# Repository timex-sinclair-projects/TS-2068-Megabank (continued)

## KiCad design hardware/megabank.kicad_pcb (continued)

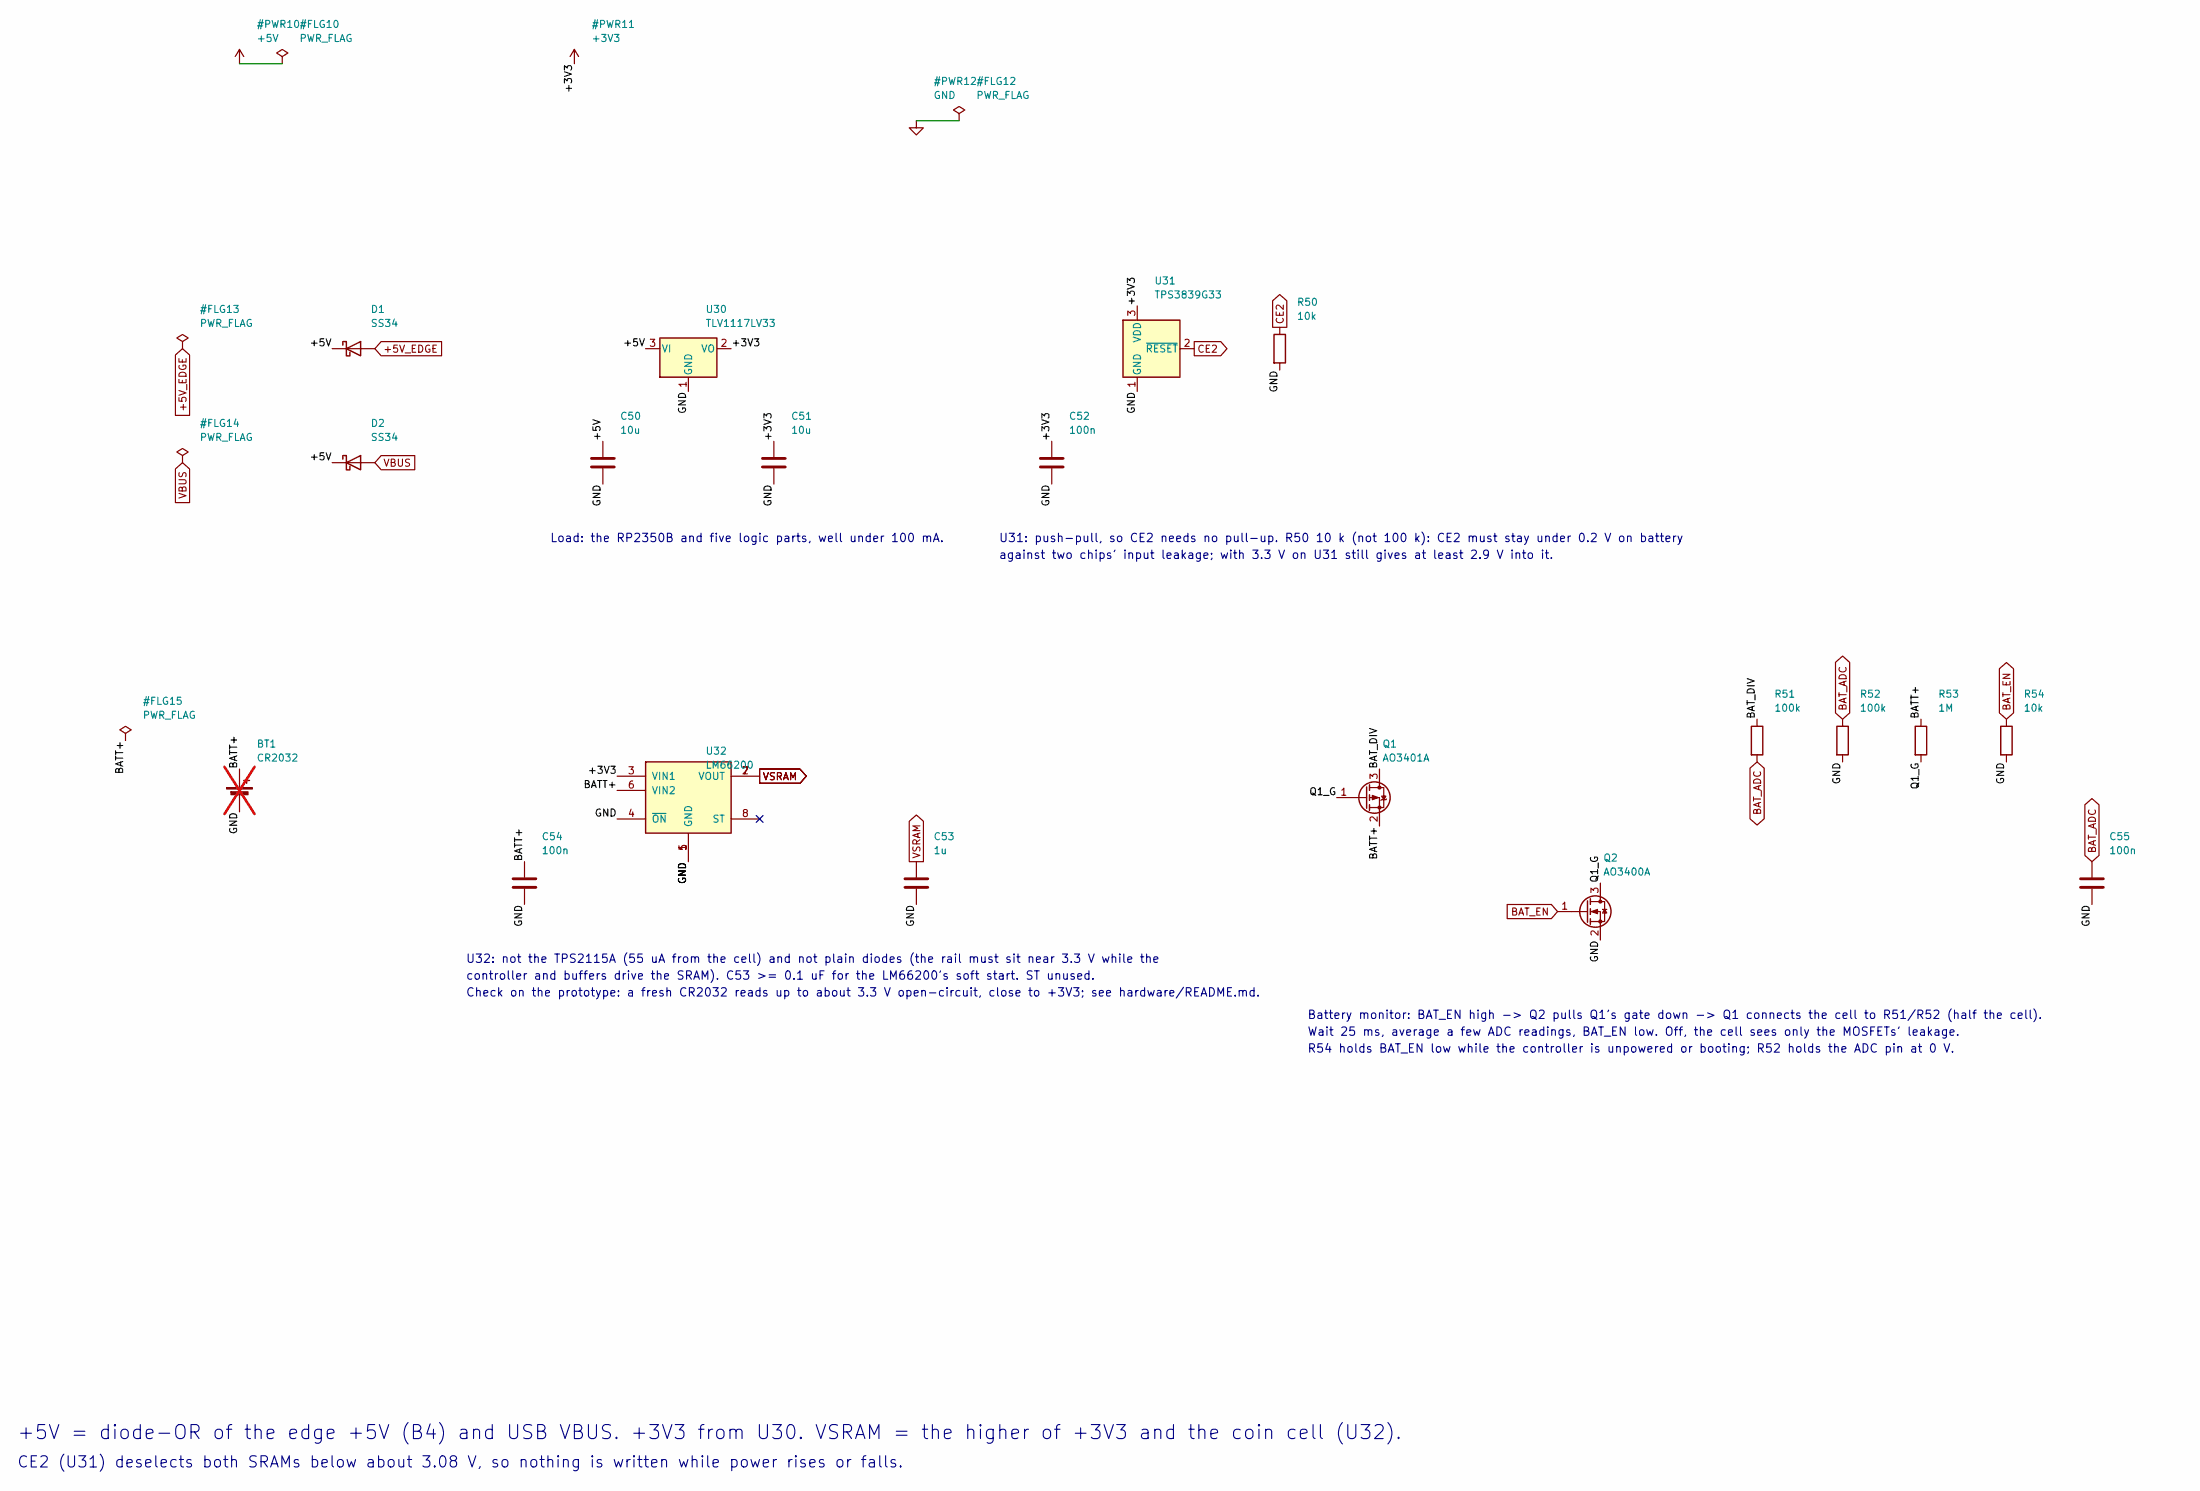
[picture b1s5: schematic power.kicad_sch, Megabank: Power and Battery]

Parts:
BT1: CR2032; BatteryHolder_Keystone_3034_1x20mm; MPN 3034; not fitted
C50, C51: 10u; C_0603_1608Metric; MPN CL10A106KP8NNNC; LCSC C19702
C52, C54, C55: 100n; C_0603_1608Metric; MPN CC0603KRX7R9BB104; LCSC C14663
C53: 1u; C_0603_1608Metric; MPN CL10A105KB8NNNC; LCSC C15849
D1, D2: SS34; D_SMA; MPN SS34; LCSC C8678
Q1: AO3401A; SOT-23; MPN AO3401A; LCSC C15127
Q2: AO3400A; SOT-23; MPN AO3400A; LCSC C20917
R50, R54: 10k; R_0603_1608Metric; MPN 0603WAF1002T5E; LCSC C25804
R51, R52: 100k; R_0603_1608Metric; MPN 0603WAF1003T5E; LCSC C25803
R53: 1M; R_0603_1608Metric; MPN 0603WAF1004T5E; LCSC C22935
U30: TLV1117LV33; SOT-223-3_TabPin2; MPN TLV1117LV33DCYR; LCSC C15578
U31: TPS3839G33; SOT-23; MPN TPS3839G33DBZR; LCSC C485802
U32: LM66200; SOT-583-8; MPN LM66200DRLR; LCSC C3235556

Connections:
+3V3: C51.1, C52.1, U30.2 (VO), U31.3 (VDD), U32.3 (VIN1); also elsewhere on the board
+5V: C50.1, D1.1 (K), D2.1 (K), U30.3 (VI)
+5V_EDGE: D1.2 (A); also elsewhere on the board
/Power and Battery/BATT+: BT1.1 (+), C54.1, Q1.2 (S), R53.1, U32.6 (VIN2)
/Power and Battery/BAT_DIV: Q1.3 (D), R51.1
/Power and Battery/Q1_G: Q1.1 (G), Q2.3 (D), R53.2
BAT_ADC: C55.1, R51.2, R52.1; also elsewhere on the board
BAT_EN: Q2.1 (G), R54.1; also elsewhere on the board
CE2: R50.1, U31.2 (~RESET); also elsewhere on the board
GND: BT1.2 (-), C50.2, C51.2, C52.2, C53.2, C54.2, C55.2, Q2.2 (S), R50.2, R52.2, R54.2, U30.1 (GND), U31.1 (GND), U32.1 (GND), U32.4 (~ON), U32.5 (GND); also elsewhere on the board
VBUS: D2.2 (A); also elsewhere on the board
VSRAM: C53.1, U32.2 (VOUT), U32.7 (VOUT); also elsewhere on the board

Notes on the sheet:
+5V = diode-OR of the edge +5V (B4) and USB VBUS. +3V3 from U30. VSRAM = the higher of +3V3 and the coin cell (U32).
CE2 (U31) deselects both SRAMs below about 3.08 V, so nothing is written while power rises or falls.
Load: the RP2350B and five logic parts, well under 100 mA.
U31: push-pull, so CE2 needs no pull-up. R50 10 k (not 100 k): CE2 must stay under 0.2 V on battery
against two chips' input leakage; with 3.3 V on U31 still gives at least 2.9 V into it.
U32: not the TPS2115A (55 uA from the cell) and not plain diodes (the rail must sit near 3.3 V while the
controller and buffers drive the SRAM). C53 >= 0.1 uF for the LM66200's soft start. ST unused.
Check on the prototype: a fresh CR2032 reads up to about 3.3 V open-circuit, close to +3V3; see hardware/README.md.
Battery monitor: BAT_EN high -> Q2 pulls Q1's gate down -> Q1 connects the cell to R51/R52 (half the cell).
Wait 25 ms, average a few ADC readings, BAT_EN low. Off, the cell sees only the MOSFETs' leakage.
R54 holds BAT_EN low while the controller is unpowered or booting; R52 holds the ADC pin at 0 V.

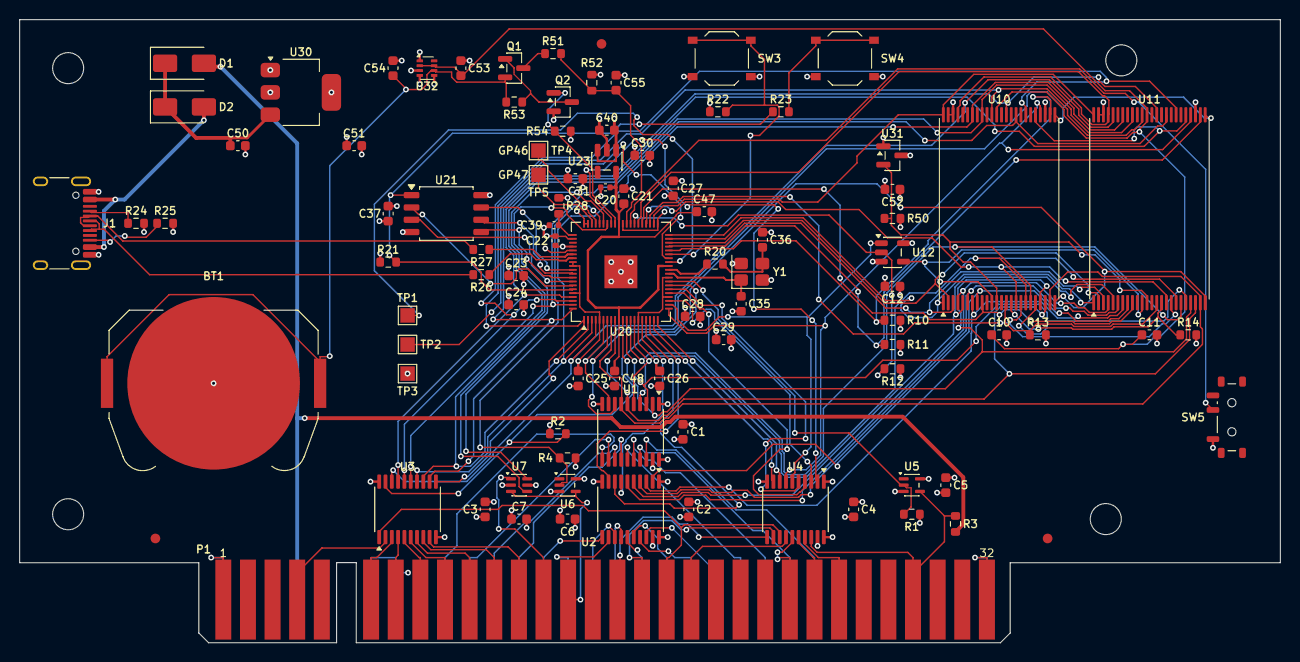
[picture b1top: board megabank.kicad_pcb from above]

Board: 4 copper layers, 130.0 x 64.2 mm, 97 parts (0 on the bottom side), 121 nets.

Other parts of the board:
FID1, FID2, FID3: Fiducial_1mm_Mask2mm
H1, H2, H3, H4: MountingHole_3.2mm_M3

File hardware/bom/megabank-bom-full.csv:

"Value","Reference","Footprint","MPN","LCSC","Qty"
"100n","C1-C7,C10-C12,C21,C23-C31,C37,C47,C48,C52,C54,C55","Capacitor_SMD:C_0603_1608Metric","CC0603KRX7R9BB104","C14663","26"
"4.7u","C20,C22,C39","Capacitor_SMD:C_0402_1005Metric","CL05A475MP5NRNC","C23733","3"
"15p","C35,C36","Capacitor_SMD:C_0603_1608Metric","CL10C150JB8NNNC","C1644","2"
"1u","C40,C53","Capacitor_SMD:C_0603_1608Metric","CL10A105KB8NNNC","C15849","2"
"10u","C50,C51","Capacitor_SMD:C_0603_1608Metric","CL10A106KP8NNNC","C19702","2"
"SS34","D1,D2","Diode_SMD:D_SMA","SS34","C8678","2"
"USB-C","J1","Connector_USB:USB_C_Receptacle_HRO_TYPE-C-31-M-12","TYPE-C-31-M-12","C165948","1"
"TS2068_Edge","P1","megabank:TS2068_EdgeConnector_2x32","","","1"
"AO3401A","Q1","Package_TO_SOT_SMD:SOT-23","AO3401A","C15127","1"
"AO3400A","Q2","Package_TO_SOT_SMD:SOT-23","AO3400A","C20917","1"
"10k","R1,R2,R4,R10-R12,R21,R22,R50,R54","Resistor_SMD:R_0603_1608Metric","0603WAF1002T5E","C25804","10"
"0","R13,R14","Resistor_SMD:R_0603_1608Metric","0603WAF0000T5E","C21189","2"
"1k","R20,R23","Resistor_SMD:R_0603_1608Metric","0603WAF1001T5E","C21190","2"
"5k1","R24,R25","Resistor_SMD:R_0603_1608Metric","0603WAF5101T5E","C23186","2"
"33","R26-R28","Resistor_SMD:R_0603_1608Metric","0603WAF330JT5E","C23140","3"
"100k","R51,R52","Resistor_SMD:R_0603_1608Metric","0603WAF1003T5E","C25803","2"
"1M","R53","Resistor_SMD:R_0603_1608Metric","0603WAF1004T5E","C22935","1"
"RUN","SW3","Button_Switch_SMD:SW_Push_1P1T_XKB_TS-1187A","TS-1187A-B-A-B","C318884","1"
"BOOTSEL","SW4","Button_Switch_SMD:SW_Push_1P1T_XKB_TS-1187A","TS-1187A-B-A-B","C318884","1"
"WP","SW5","Button_Switch_SMD:SW_SPDT_Shouhan_MSK12C02","MSK12C02","C431540","1"
"SWCLK","TP1","TestPoint:TestPoint_Pad_1.5x1.5mm","","","1"
"SWDIO","TP2","TestPoint:TestPoint_Pad_1.5x1.5mm","","","1"
"GND","TP3","TestPoint:TestPoint_Pad_1.5x1.5mm","","","1"
"GP46","TP4","TestPoint:TestPoint_Pad_1.5x1.5mm","","","1"
"GP47","TP5","TestPoint:TestPoint_Pad_1.5x1.5mm","","","1"
"74LVC245APW","U1-U4","Package_SO:TSSOP-20_4.4x6.5mm_P0.65mm","74LVC245APW,118","C6082","4"
"74LVC1G06","U5,U6","Package_TO_SOT_SMD:SOT-353_SC-70-5","SN74LVC1G06DCKR","C7828","2"
"74LVC2G34","U7","Package_TO_SOT_SMD:SOT-363_SC-70-6","SN74LVC2G34DCKR","C14461","1"
"CY62167EV30LL-45ZXIT","U10,U11","Package_SO:TSOP-I-48_18.4x12mm_P0.5mm","CY62167EV30LL-45ZXIT","C511152","2"
"SN74LVC1G32DBVR","U12","Package_TO_SOT_SMD:SOT-23-5","SN74LVC1G32DBVR","C10096","1"
"RP2350B","U20","Package_DFN_QFN:QFN-80-1EP_10x10mm_P0.4mm_EP3.4x3.4mm","RP2350B","C42415655","1"
"GD25Q128ESIGR","U21","Package_SO:SOIC-8_5.3x5.3mm_P1.27mm","GD25Q128ESIGR","C2928891","1"
"ME6211C12M5G-N","U23","Package_TO_SOT_SMD:SOT-23-5","ME6211C12M5G-N","C236672","1"
"TLV1117LV33","U30","Package_TO_SOT_SMD:SOT-223-3_TabPin2","TLV1117LV33DCYR","C15578","1"
"TPS3839G33","U31","Package_TO_SOT_SMD:SOT-23","TPS3839G33DBZR","C485802","1"
"LM66200","U32","Package_TO_SOT_SMD:SOT-583-8","LM66200DRLR","C3235556","1"
"12MHz","Y1","Crystal:Crystal_SMD_3225-4Pin_3.2x2.5mm","ABM8-272-T3","C20625731","1"

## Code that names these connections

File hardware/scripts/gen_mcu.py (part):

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Dropped from v3: the PSRAM (U22, C38) and the core regulator's inductor L1. Added: SW5,
the write-protect switch; U23, an ME6211C12 LDO that supplies DVDD at 1.2 V in place of
the on-chip switcher (RP2350 datasheet 6.3.7; as on the OpenSpand card), with C40 at its
input and C20 at its output; TP4/TP5 on the spare GPIO46/47, for bench experiments.

GPIO map (docs/spec.md "Pins"). PIO windows: a state machine sees 32 pins, from GPIO0
or GPIO16, so everything both programs need sits in GPIO16-31:
  GPIO0-7    SD0-SD7       SRAM-side data (port reads and writes)        window 0
  GPIO8-15   BA0-BA7       port decode                                     window 0
  GPIO16-18  BA13-BA15     chunk number (out pc, 3)                        both
  GPIO19-25  nMREQ_L nIORQ_L nRD_L nWR_L nRFSH_L nM1_L nRESET_L            both
  GPIO26     nDOE          data buffer enable (R2 pull-up)                 both
  GPIO27     BE_REQ        to U5 -> /BE (R1 pull-down)                     both
  GPIO28-29  nCE1_0/1      SRAM chip enables (R10/R11 pull-downs)          window 16
  GPIO30-37  PA13-PA20     page bits, contiguous after the ~CE1s           window 16
  GPIO38     WINH          write inhibit (R12 pull-up)                     window 16
  GPIO39     nWP           write-protect switch, low = protected (internal pull-up)
  GPIO40     BAT_ADC       ADC0
  GPIO41     BAT_EN
  GPIO42     nBE_L         /BE read back
  GPIO43     nINT_L        /INT, through U7                                window 16
  GPIO44     nNMI_L        /NMI, through U7                                window 16
  GPIO45     NMI_REQ       to U6 -> /NMI (R4 pull-down)                    window 16
  GPIO46-47  GP46, GP47    spare, to test pads TP4/TP5 (bench experiments)
"""
import os
import sys
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        if nm in ("IOVDD", "QSPI_IOVDD", "USB_OTP_VDD", "ADC_AVDD", "VREG_VIN"):
            s.label("+3V3", U.pin(num))
        elif nm == "VREG_AVDD":
            s.label("VREG_AVDD", U.pin(num))
        elif nm in ("GND", "VREG_PGND"):
            s.label("GND", U.pin(num))
        elif nm == "DVDD":
            s.label("DVDD", U.pin(num))
    s.nc(U.pin(by_name["VREG_LX"]))                 # on-chip switcher unused: no inductor
    s.label("GND", U.pin(by_name["VREG_FB"]))       # datasheet 6.3.7: FB to ground when DVDD comes from outside
    s.label("XIN", U.pin(by_name["XIN"])); s.label("XOUT", U.pin(by_name["XOUT"]))
    s.label("SWCLK", U.pin(by_name["SWCLK"])); s.label("SWDIO", U.pin(by_name["SWDIO"]))
    s.label("RUN", U.pin(by_name["RUN"]))
    s.label("USB_DM", U.pin(by_name["USB_DM"])); s.label("USB_DP", U.pin(by_name["USB_DP"]))
    for nm in ("QSPI_SD0", "QSPI_SD1", "QSPI_SD2", "QSPI_SD3", "QSPI_SCLK"):
        s.label(nm, U.pin(by_name[nm]))
    s.label("nQSPI_SS", U.pin(by_name["~{QSPI_SS}"]))

    # ---- core supply: ME6211C12 LDO (U23) -> DVDD 1.2 V, in place of the on-chip switcher ----------
    # The switcher's inductor (Abracon AOTA-B201610, L1 on v3) is the scarcest part on the board, so
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    # stay powered: the chip's power-on reset runs from them. Firmware may put the regulator in HIZ.
    LDO = s.place("Regulator_Linear:ME6211C12M5", "U23", "ME6211C12M5G-N", SOT23_5, 250, 60)
    s.label("+3V3", LDO.pin("1")); s.label("GND", LDO.pin("2")); s.label("+3V3", LDO.pin("3"))
    s.nc(LDO.pin("4")); s.label("DVDD", LDO.pin("5"))
    for k, (ref, net, val, fp) in enumerate([("C40", "+3V3", "1u", C0603), ("C20", "DVDD", "4.7u", C0402), ("C22", "+3V3", "4.7u", C0402), ("C21", "DVDD", "100n", C0603), ("C47", "DVDD", "100n", C0603), ("C48", "DVDD", "100n", C0603)]):
        C = s.place("Device:C", ref, val, fp, 265 + 10 * k, 60)
        s.label(net, C.pin("1")); s.label("GND", C.pin("2"))
    s.text("U23 ME6211C12M5G-N: DVDD 1.2 V (v3 runs the core at 1.2 V for 250 MHz). C40 1 uF in, C20 4.7 uF out. VREG_LX open, VREG_FB to GND.", 245, 75, 1.5)
    s.text("C22 at VREG_VIN (0402 as in the design guide). C21/C47/C48: 100 nF at DVDD pins 51, 32, 10.", 245, 78, 1.5)
    R28 = s.place("Device:R", "R28", "33", R0603, 300, 85)
    s.label("+3V3", R28.pin("1")); s.label("VREG_AVDD", R28.pin("2"))
    C39 = s.place("Device:C", "C39", "4.7u", C0402, 315, 85)
    s.label("VREG_AVDD", C39.pin("1")); s.label("GND", C39.pin("2"))
    s.text("R28/C39: 33 R + 4.7 uF filter on VREG_AVDD (design guide R3/C9).", 245, 95, 1.5)
    FL2 = s.place("power:PWR_FLAG", "#FLG08", "PWR_FLAG", "", 330, 85)
    s.label("VREG_AVDD", FL2.pin("1"))

    # ---- IOVDD and analog decoupling: 12 x 100 nF ----------------------------------
    for k in range(9):
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
    # ---- crystal ---------------------------------------------------------------------
    Y1 = s.place("Device:Crystal_GND24", "Y1", "12MHz", "Crystal:Crystal_SMD_3225-4Pin_3.2x2.5mm", 270, 150)
    s.label("XIN", Y1.pin("1")); s.label("XOUT_R", Y1.pin("3")); s.label("GND", Y1.pin("2")); s.label("GND", Y1.pin("4"))
    R20 = s.place("Device:R", "R20", "1k", R0603, 295, 150)
    s.label("XOUT", R20.pin("1")); s.label("XOUT_R", R20.pin("2"))
    C35 = s.place("Device:C", "C35", "15p", C0603, 255, 165)
    s.label("XIN", C35.pin("1")); s.label("GND", C35.pin("2"))
    C36 = s.place("Device:C", "C36", "15p", C0603, 285, 165)
    s.label("XOUT_R", C36.pin("1")); s.label("GND", C36.pin("2"))
    s.text("Y1: 12 MHz, e.g. ABM8-272-T3 (CL 10 pF). C35/C36 15 pF, R20 1 k in series with XOUT.", 245, 180, 1.5)

    # ---- QSPI flash and PSRAM ---------------------------------------------------------
    F = s.place("Memory_Flash:W25Q128JVS", "U21", "GD25Q128ESIGR", "Package_SO:SOIC-8_5.3x5.3mm_P1.27mm", 340, 150)
    s.label("nQSPI_SS", F.pin("1")); s.label("QSPI_SD1", F.pin("2")); s.label("QSPI_SD2", F.pin("3")); s.label("GND", F.pin("4"))
    s.label("QSPI_SD0", F.pin("5")); s.label("QSPI_SCLK", F.pin("6")); s.label("QSPI_SD3", F.pin("7")); s.label("+3V3", F.pin("8"))
    C = s.place("Device:C", "C37", "100n", C0603, 375, 175)
    s.label("+3V3", C.pin("1")); s.label("GND", C.pin("2"))
    R21 = s.place("Device:R", "R21", "10k", R0603, 395, 150)
    s.label("+3V3", R21.pin("1")); s.label("nQSPI_SS", R21.pin("2"))
    s.text("U21 boot flash (XIP CS0), C37 at U21. Holds the firmware and the settings (BASE, SIZE).", 320, 225, 1.5)

    # ---- RUN and BOOTSEL -------------------------------------------------------------
    R22 = s.place("Device:R", "R22", "10k", R0603, 250, 210)
    s.label("+3V3", R22.pin("1")); s.label("RUN", R22.pin("2"))
    SW3 = s.place("Switch:SW_Push", "SW3", "RUN", SW_FP, 270, 225)
    s.label("RUN", SW3.pin("1")); s.label("GND", SW3.pin("2"))
    R23 = s.place("Device:R", "R23", "1k", R0603, 250, 245)
    s.label("nQSPI_SS", R23.pin("1")); s.label("BOOTSEL_SW", R23.pin("2"))
    SW4 = s.place("Switch:SW_Push", "SW4", "BOOTSEL", SW_FP, 270, 260)
    s.label("BOOTSEL_SW", SW4.pin("1")); s.label("GND", SW4.pin("2"))

    # ---- USB-C, data only -----------------------------------------------------------
    J1 = s.place("Connector:USB_C_Receptacle_USB2.0_16P", "J1", "USB-C", "Connector_USB:USB_C_Receptacle_HRO_TYPE-C-31-M-12", 40, 60)
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        s.nc(J1.pin(pin))
    for pin in ("A1", "A12", "B1", "B12", "SH"):
        s.label("GND", J1.pin(pin))
    s.label("USB_DP_C", J1.pin("A6")); s.label("USB_DP_C", J1.pin("B6"))
    s.label("USB_DM_C", J1.pin("A7")); s.label("USB_DM_C", J1.pin("B7"))
    s.label("CC1", J1.pin("A5")); s.label("CC2", J1.pin("B5"))
    R24 = s.place("Device:R", "R24", "5k1", R0603, 80, 40)
    s.label("CC1", R24.pin("1")); s.label("GND", R24.pin("2"))
    R25 = s.place("Device:R", "R25", "5k1", R0603, 95, 40)
    s.label("CC2", R25.pin("1")); s.label("GND", R25.pin("2"))
    R26 = s.place("Device:R", "R26", "33", R0603, 80, 85)
    s.label("USB_DP_C", R26.pin("1")); s.label("USB_DP", R26.pin("2"))
    R27 = s.place("Device:R", "R27", "33", R0603, 95, 85)
    s.label("USB_DM_C", R27.pin("1")); s.label("USB_DM", R27.pin("2"))
    s.text("J1: USB 2.0. VBUS -> power sheet. SBU unconnected.", 20, 100, 1.5)
    s.text("R24/R25 5.1 k Rd. R26/R27 33 R series (JLC basic; 27 R is not).", 20, 103, 1.5)

    # ---- write-protect switch -------------------------------------------------------
    SW5 = s.place("Switch:SW_SPDT", "SW5", "WP", SLIDE_FP, 270, 280)
    s.glabel("nWP", SW5.pin("B"), IN); s.label("GND", SW5.pin("A")); s.nc(SW5.pin("C"))
    s.text("SW5: write protect. Common to GPIO39 (internal pull-up); one throw to ground = protected, the other open.", 245, 292, 1.5)

    # ---- SWD pads ---------------------------------------------------------------------
    for k, (ref, net) in enumerate([("TP1", "SWCLK"), ("TP2", "SWDIO"), ("TP3", "GND")]):
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    for k, (ref, net) in enumerate([("TP4", "GP46"), ("TP5", "GP47")]):
        T = s.place("Connector:TestPoint", ref, net, TP_FP, 100 + 15 * k, 250)
        s.label(net, T.pin("1"))
    s.text("TP4/TP5: spare GPIO46/47, for bench experiments (a second controller's handshake).", 90, 262, 1.5)

    s.write()
    print("wrote mcu.kicad_sch")
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
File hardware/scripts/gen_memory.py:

#!/usr/bin/env python3
"""Generate memory.kicad_sch: the 4 MB of SRAM.

  U10, U11  CY62167EV30LL-45ZXIT (16 Mbit, TSOP I 48), each used as 2M x 8: BYTE to
            ground, pin 45 (I/O15/A20) is A20, I/O8-I/O14 unused. 4 MB in two chips.
            A0-A12   <- BA0-BA12, the buffered Z80 address
            A13-A20  <- PA13-PA20, the page bits from the controller
            I/O0-7  <-> SD0-SD7, the data buffer's SRAM side (and the controller's GPIO0-7)
            ~CE1     <- nCE1_0 / nCE1_1 from the controller: the 9th page bit picks the chip
            CE2      <- CE2 from the supervisor (power sheet): low deselects whatever ~CE1 does
            ~OE      <- nRD_L;  ~WE <- nSWE from U12
            VCC      <- VSRAM, the battery-backed rail
  U12       SN74LVC1G32: nSWE = nWR_L OR WINH (the controller's per-chunk write inhibit)
  R10, R11  ~CE1 pull-downs: at a logic level on battery (a pull-up to VSRAM would feed the
            unpowered RP2350B); CE2 low keeps the chips deselected
  R12       WINH pull-up: Z80 writes cannot reach the SRAM until the firmware runs
  R13, R14  0 R, BHE and BLE to ground: fitted for the EV30 (needs them at a logic level
            for its standby figures), do not place for a DV30 (marks them "leave floating")
SRAM address and data lines may be permuted freely at layout (both chips see the same
permutation through the same Z80 and page bits), except that SDn must stay the
controller's GPIOn: the controller answers IN FCh/FDh on the same bus.
"""
import os
import sys

sys.path.insert(0, os.path.dirname(os.path.abspath(__file__)))
from schlib import Sheet  # noqa: E402

TSOP48 = "Package_SO:TSOP-I-48_18.4x12mm_P0.5mm"
SOT23_5 = "Package_TO_SOT_SMD:SOT-23-5"
R0603 = "Resistor_SMD:R_0603_1608Metric"
C0603 = "Capacitor_SMD:C_0603_1608Metric"

OUT, IN, BI = "output", "input", "bidirectional"


def main():
    s = Sheet("megabank.kicad_sch", "memory.kicad_sch", "Megabank: SRAM")
    s.text("4 MB: two CY62167EV30 as 2M x 8. SRAM address = page x 8K + A12..A0; the page's 9th bit picks the chip through the ~CE1s.", 20, 285, 2.5)
    s.text("Alternate fit: CY62167DV30LL-55ZXIT, same footprint and pinout; leave R13 and R14 off for it.", 20, 290, 2.0)

    s.power("+3V3", 330, 30, "#PWR03", flag=False)
    s.power("GND", 360, 40, "#PWR04", flag=False)

    for k, (ref, ce1) in enumerate((("U10", "nCE1_0"), ("U11", "nCE1_1"))):
        U = s.place("megabank:CY62167EV30xx-ZXI", ref, "CY62167EV30LL-45ZXIT", TSOP48, 80 + 120 * k, 130)
        for i in range(13):
            s.glabel(f"BA{i}", U.pin(f"A{i}"), IN)
        for i in range(13, 20):
            s.glabel(f"PA{i}", U.pin(f"A{i}"), IN)
        s.glabel("PA20", U.pin("I/O15/A20"), IN)
        for i in range(8):
            s.glabel(f"SD{i}", U.pin(f"I/O{i}"), BI)
        for i in range(8, 15):
            s.nc(U.pin(f"I/O{i}"))
        s.glabel(ce1, U.pin("~{CE1}"), IN)
        s.glabel("CE2", U.pin("CE2"), IN)
        s.glabel("nRD_L", U.pin("~{OE}"), IN)
        s.label("nSWE", U.pin("~{WE}"))
        s.label("BHE", U.pin("~{BHE}")); s.label("BLE", U.pin("~{BLE}"))
        s.label("GND", U.pin("BYTE"))
        s.glabel("VSRAM", U.pin("37"), IN)
        s.label("GND", U.pin("27")); s.label("GND", U.pin("46"))

    # ---- /WE gate ---------------------------------------------------------------
    U12 = s.place("74xGxx:74LVC1G32", "U12", "SN74LVC1G32DBVR", SOT23_5, 320, 120)
    s.glabel("nWR_L", U12.pin("1"), IN); s.glabel("WINH", U12.pin("2"), IN); s.label("nSWE", U12.pin("4"))
    s.label("+3V3", U12.pin("5")); s.label("GND", U12.pin("3"))
    s.text("U12: ~WE = nWR_L OR WINH. WINH is set per chunk from WPROT and the switch, and pulled up (R12).", 290, 135, 1.5)

    # ---- pulls and the BHE/BLE links ------------------------------------------------
    pulls = [("R10", "nCE1_0", "GND", "10k"), ("R11", "nCE1_1", "GND", "10k"), ("R12", "WINH", "+3V3", "10k"),
             ("R13", "BHE", "GND", "0"), ("R14", "BLE", "GND", "0")]
    for k, (ref, net, rail, val) in enumerate(pulls):
        R = s.place("Device:R", ref, val, R0603, 300 + 15 * k, 170)
        if net in ("BHE", "BLE"):
            s.label(net, R.pin("1"))
        else:
            s.glabel(net, R.pin("1"), IN)
        s.label(rail, R.pin("2"))
    s.text("R10/R11: ~CE1 pull-downs (to ground, not VSRAM). R13/R14: fit for the EV30, DNP for a DV30 build.", 290, 185, 1.5)

    # ---- decoupling: 100 nF at each SRAM (VSRAM), 100 nF at U12 ----------------------
    for k, (ref, net) in enumerate((("C10", "VSRAM"), ("C11", "VSRAM"), ("C12", "+3V3"))):
        C = s.place("Device:C", ref, "100n", C0603, 40 + 9 * k, 255)
        if net == "VSRAM":
            s.glabel(net, C.pin("1"), IN)
        else:
            s.label(net, C.pin("1"))
        s.label("GND", C.pin("2"))

    s.write()
    print("wrote memory.kicad_sch")


if __name__ == "__main__":
    main()

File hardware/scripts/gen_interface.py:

#!/usr/bin/env python3
"""Generate interface.kicad_sch: the 2068 side of the Megabank.

Contents (docs/spec.md, "Hardware"):
  P1   TS2068 edge connector (v3's gold fingers)
  U1   74LVC245  Z80 A0-A7  -> BA0-BA7     always on (fixed B->A): port decode, SRAM A0-A7
  U2   74LVC245  Z80 A8-A15 -> BA8-BA15    always on: SRAM A8-A12, chunk A13-A15
  U3   74LVC245  Z80 D0-D7 <-> SD0-SD7     DIR = /RD, /OE = nDOE from the controller
  U4   74LVC245  Z80 control -> 3.3 V copies for the controller (fixed B->A)
  U5   74LVC1G06 open-drain inverter: BE_REQ -> /BE (wire-ORs with v3's 74LVC06)
  R1   BE_REQ pull-down (boot does not rely on the RP2350's internal pull-down, erratum E9)
  R2   nDOE pull-up: the data buffer stays off the bus until the firmware runs
  R3   /BE pull-up to the 2068's +5V, DNP: the bus already has v3's 2k2 (R14 on v3);
       fit it only if open question 13 says the board needs its own
  U6   74LVC1G06 open-drain inverter: NMI_REQ -> /NMI (wire-ORs with v3's NMI driver and button)
  R4   NMI_REQ pull-down, as R1
  U7   74LVC2G34 /INT and /NMI -> 3.3 V copies (nINT_L, nNMI_L) for the controller
       (spec, open question 16). /NMI's pull-up is the 2068's own, as for v3.
Unlike v3 the address buffers are not a byte mux: the SRAM needs A0-A12 on
every memory cycle, so every address bit has its own 3.3 V net (BAn).
Net naming: n<NAME> = active low; _L = 3.3 V copy of a bus signal.
"""
import os
import sys

sys.path.insert(0, os.path.dirname(os.path.abspath(__file__)))
from schlib import Sheet  # noqa: E402

TSSOP20 = "Package_SO:TSSOP-20_4.4x6.5mm_P0.65mm"
SC70_5 = "Package_TO_SOT_SMD:SOT-353_SC-70-5"
SC70_6 = "Package_TO_SOT_SMD:SOT-363_SC-70-6"
R0603 = "Resistor_SMD:R_0603_1608Metric"
C0603 = "Capacitor_SMD:C_0603_1608Metric"

OUT, IN, BI = "output", "input", "bidirectional"


def main():
    s = Sheet("megabank.kicad_sch", "interface.kicad_sch", "Megabank: 2068 Interface")
    s.text("2068 bus interface. Nets: n = active low, _L = 3.3 V copy of a bus signal, BAn = buffered address, SDn = SRAM-side data.", 20, 285, 2.5)
    s.text("Power: edge +5V (B4) goes to the power sheet as +5V_EDGE. +15V (B3) unused. LVC inputs take the 2068's 5 V; a 3.3 V high is a TTL high.", 20, 290, 2.0)

    # ---- P1 edge connector -------------------------------------------------
    P1 = s.place("megabank:TS2068_Edge", "P1", "TS2068_Edge", "megabank:TS2068_EdgeConnector_2x32", 60, 120)
    used = {
        "A1": "GND", "B1": "GND", "A32": "GND", "B32": "GND", "B7": "GND", "B8": "GND",
        "A4": "D7", "A7": "D0", "A8": "D1", "A9": "D2", "A10": "D6", "A11": "D5", "A12": "D3", "A13": "D4",
        "A17": "nMREQ", "A18": "nIORQ", "A19": "nRD", "A20": "nWR", "A24": "nRESET",
        "A25": "nM1", "A26": "nRFSH", "A29": "nBE", "A14": "nINT", "A15": "nNMI",
        "B10": "A0", "B11": "A1", "B12": "A2", "B13": "A3",
        "B14": "A15", "B15": "A14", "B16": "A13", "B17": "A12", "B18": "A11", "B19": "A10", "B20": "A9", "B21": "A8",
        "B22": "A7", "B23": "A6", "B24": "A5", "B25": "A4",
    }
    for pin, net in used.items():
        s.label(net, P1.pin(pin))
    s.glabel("+5V_EDGE", P1.pin("B4"), OUT)
    for side in "AB":
        for pos in range(1, 33):
            pin = f"{side}{pos}"
            if pos != 6 and pin not in used and pin != "B4":
                s.nc(P1.pin(pin))

    s.power("+3V3", 330, 30, "#PWR01", flag=False)
    s.power("GND", 360, 40, "#PWR02", flag=False)

    def transceiver(ref, x, y):
        return s.place("74xx:74LS245", ref, "74LVC245APW", TSSOP20, x, y)

    # ---- U1/U2 address buffers, B (Z80) -> A (3.3 V), always enabled ----------------
    # Finger order (left to right): A0 A1 A2 A3 | A15 ... A8 | A7 A6 A5 A4. As on v3, U2 sits
    # over the middle eight fingers and U1 in the row above, its B pins in finger order
    # (A0-A3 from the left, A7-A4 from the right); at rot 270 B7 is the leftmost pin.
    U1 = transceiver("U1", 150, 50)
    for b_, idx in zip(range(7, -1, -1), [0, 1, 2, 3, 7, 6, 5, 4]):
        s.label(f"A{idx}", U1.pin(f"B{b_}"))
        s.glabel(f"BA{idx}", U1.pin(f"A{b_}"), OUT)
    U2 = transceiver("U2", 150, 110)
    for b_, idx in zip(range(7, -1, -1), [15, 14, 13, 12, 11, 10, 9, 8]):
        s.label(f"A{idx}", U2.pin(f"B{b_}"))
        s.glabel(f"BA{idx}", U2.pin(f"A{b_}"), OUT)
    for U in (U1, U2):
        s.label("GND", U.pin("1"))       # DIR low: B -> A
        s.label("GND", U.pin("19"))      # always enabled
        s.label("+3V3", U.pin("20")); s.label("GND", U.pin("10"))

    # ---- U3 data transceiver: A = Z80 (faces the fingers), B = SD bus ---------------
    # DIR = /RD straight from the bus: low on a read = B -> A (board -> Z80). The SRAM's
    # data bits may be permuted freely at layout; the controller's GPIO0-7 may not.
    U3 = transceiver("U3", 150, 170)
    for b_, idx in zip(range(8), [7, 0, 1, 2, 6, 5, 3, 4]):
        s.label(f"D{idx}", U3.pin(f"A{b_}"))
        s.glabel(f"SD{idx}", U3.pin(f"B{b_}"), BI)
    s.label("nRD", U3.pin("1"))
    s.glabel("nDOE", U3.pin("19"), IN)
    s.label("+3V3", U3.pin("20")); s.label("GND", U3.pin("10"))

    # ---- U4 control inputs, B (Z80) -> A (3.3 V), in finger order ----------------------
    U4 = transceiver("U4", 150, 230)
    ctl = ["nMREQ", "nIORQ", "nRD", "nWR", "nRESET", "nM1", "nRFSH", "nBE"]
    for b_, src in zip(range(7, -1, -1), ctl):
        s.label(src, U4.pin(f"B{b_}"))
        s.glabel(src + "_L", U4.pin(f"A{b_}"), OUT)
    s.label("GND", U4.pin("1")); s.label("GND", U4.pin("19"))
    s.label("+3V3", U4.pin("20")); s.label("GND", U4.pin("10"))
    s.text("U4's eighth channel reads /BE back (nBE_L), for bench timing and to see v3 serving a chunk.", 120, 265, 1.5)

    # ---- U5 /BE driver ------------------------------------------------------------------
    U5 = s.place("74xGxx:74LVC1G06", "U5", "74LVC1G06", SC70_5, 260, 60)
    s.glabel("BE_REQ", U5.pin("2"), IN); s.label("nBE", U5.pin("4"))
    s.label("+3V3", U5.pin("5")); s.label("GND", U5.pin("3"))
    R1 = s.place("Device:R", "R1", "10k", R0603, 290, 60)
    s.glabel("BE_REQ", R1.pin("1"), IN); s.label("GND", R1.pin("2"))
    R2 = s.place("Device:R", "R2", "10k", R0603, 305, 60)
    s.label("+3V3", R2.pin("1")); s.glabel("nDOE", R2.pin("2"), IN)
    R3 = s.place("Device:R", "R3", "2k2", R0603, 320, 60, dnp=True)
    s.glabel("+5V_EDGE", R3.pin("1"), IN); s.label("nBE", R3.pin("2"))
    s.text("U5: open drain, so it wire-ORs with v3's 74LVC06 on /BE. R1: BE_REQ held low (released) until the firmware runs.", 245, 80, 1.5)
    s.text("R2: data buffer held off. R3 (DNP): /BE pull-up to the 2068's +5V, only if the bus's own (v3's 2k2) proves weak.", 245, 83, 1.5)

    # ---- /INT and /NMI: U6 /NMI driver, U7 input buffers ---------------------------------
    U6 = s.place("74xGxx:74LVC1G06", "U6", "74LVC1G06", SC70_5, 260, 120)
    s.glabel("NMI_REQ", U6.pin("2"), IN); s.label("nNMI", U6.pin("4"))
    s.label("+3V3", U6.pin("5")); s.label("GND", U6.pin("3"))
    R4 = s.place("Device:R", "R4", "10k", R0603, 290, 120)
    s.glabel("NMI_REQ", R4.pin("1"), IN); s.label("GND", R4.pin("2"))
    U7a = s.place("74xGxx:74LVC2G34", "U7", "74LVC2G34", SC70_6, 260, 150, unit=1)
    s.label("nINT", U7a.pin("1")); s.glabel("nINT_L", U7a.pin("6"), OUT)
    U7b = s.place("74xGxx:74LVC2G34", "U7", "74LVC2G34", SC70_6, 260, 165, unit=2)
    s.label("nNMI", U7b.pin("3")); s.glabel("nNMI_L", U7b.pin("4"), OUT)
    U7c = s.place("74xGxx:74LVC2G34", "U7", "74LVC2G34", SC70_6, 285, 157, unit=3)
    s.label("+3V3", U7c.pin("5")); s.label("GND", U7c.pin("2"))
    s.text("U6: open drain, like U5; R4 holds NMI_REQ low (released) until the firmware runs.", 245, 135, 1.5)
    s.text("U7: /INT and /NMI in, for the controller (spec, open question 16). /NMI's pull-up is the 2068's.", 245, 180, 1.5)

    # ---- decoupling ------------------------------------------------------------
    for k in range(7):          # C1-C4: U1-U4, C5-C7: U5-U7
        C = s.place("Device:C", f"C{k + 1}", "100n", C0603, 40 + 9 * k, 255)
        s.label("+3V3", C.pin("1")); s.label("GND", C.pin("2"))

    s.write()
    print("wrote interface.kicad_sch")


if __name__ == "__main__":
    main()

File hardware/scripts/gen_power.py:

#!/usr/bin/env python3
"""Generate power.kicad_sch: supplies, battery backup and the battery monitor.

  D1, D2   SS34: +5V_EDGE (edge pin B4) and USB VBUS diode-ORed into +5V, as on v3, so
           the board can be flashed and set up from USB alone on the bench
  U30      TLV1117LV33: +3V3 for the controller, buffers and gates
  U31      TPS3839G33 supervisor on +3V3 (about 3.08 V, 200 ms): drives both SRAMs' CE2
           high only while 3.3 V is good; R50 holds CE2 low with 3.3 V gone
  U32      LM66200 ideal-diode OR: VSRAM from +3V3 (VIN1) or the battery (VIN2), 1.32 uA
  BT1      CR2032 coin cell
  Q1, Q2   battery monitor switch (docs/spec.md "Battery monitor"): the cell is read
           straight off its terminal through R51/R52 only while BAT_EN is high
Spec refs in "Battery monitor" map to: Q1 -> Q1, Q2 -> Q2, R1/R2 -> R51/R52,
R3 -> R53, R4 -> R54, C1 -> C55.
"""
import os
import sys

sys.path.insert(0, os.path.dirname(os.path.abspath(__file__)))
from schlib import Sheet  # noqa: E402

C0603 = "Capacitor_SMD:C_0603_1608Metric"
R0603 = "Resistor_SMD:R_0603_1608Metric"
D_SMA = "Diode_SMD:D_SMA"
SOT223 = "Package_TO_SOT_SMD:SOT-223-3_TabPin2"
SOT23 = "Package_TO_SOT_SMD:SOT-23"
SOT583 = "Package_TO_SOT_SMD:SOT-583-8"
BAT_FP = "Battery:BatteryHolder_Keystone_3034_1x20mm"

OUT, IN, BI = "output", "input", "bidirectional"


def main():
    s = Sheet("megabank.kicad_sch", "power.kicad_sch", "Megabank: Power and Battery")
    s.text("+5V = diode-OR of the edge +5V (B4) and USB VBUS. +3V3 from U30. VSRAM = the higher of +3V3 and the coin cell (U32).", 20, 285, 2.5)
    s.text("CE2 (U31) deselects both SRAMs below about 3.08 V, so nothing is written while power rises or falls.", 20, 290, 2.0)

    s.power("+5V", 60, 40, "#PWR10")
    s.power("+3V3", 120, 40, "#PWR11", flag=False)   # driven by U30
    s.power("GND", 180, 50, "#PWR12")

    # ---- inputs -----------------------------------------------------------------
    D1 = s.place("Device:D_Schottky", "D1", "SS34", D_SMA, 80, 90)
    s.glabel("+5V_EDGE", D1.pin("A"), IN); s.label("+5V", D1.pin("K"))
    D2 = s.place("Device:D_Schottky", "D2", "SS34", D_SMA, 80, 110)
    s.glabel("VBUS", D2.pin("A"), IN); s.label("+5V", D2.pin("K"))
    F1 = s.place("power:PWR_FLAG", "#FLG13", "PWR_FLAG", "", 50, 90)
    s.glabel("+5V_EDGE", F1.pin("1"), IN)
    F2 = s.place("power:PWR_FLAG", "#FLG14", "PWR_FLAG", "", 50, 110)
    s.glabel("VBUS", F2.pin("1"), IN)

    # ---- U30 3.3 V LDO --------------------------------------------------------------
    U30 = s.place("Regulator_Linear:TLV1117-33", "U30", "TLV1117LV33", SOT223, 140, 90)
    s.label("+5V", U30.pin("VI")); s.label("+3V3", U30.pin("VO")); s.label("GND", U30.pin("GND"))
    for k, (ref, net) in enumerate((("C50", "+5V"), ("C51", "+3V3"))):
        C = s.place("Device:C", ref, "10u", C0603, 125 + 30 * k, 110)
        s.label(net, C.pin("1")); s.label("GND", C.pin("2"))
    s.text("Load: the RP2350B and five logic parts, well under 100 mA.", 115, 125, 1.5)

    # ---- U31 supervisor -> CE2 ----------------------------------------------------------
    U31 = s.place("Power_Supervisor:TPS3839DBZ", "U31", "TPS3839G33", SOT23, 220, 90)
    s.label("+3V3", U31.pin("VDD")); s.label("GND", U31.pin("GND"))
    s.glabel("CE2", U31.pin("~{RESET}"), OUT)
    R50 = s.place("Device:R", "R50", "10k", R0603, 245, 90)
    s.glabel("CE2", R50.pin("1"), OUT); s.label("GND", R50.pin("2"))
    C52 = s.place("Device:C", "C52", "100n", C0603, 205, 110)
    s.label("+3V3", C52.pin("1")); s.label("GND", C52.pin("2"))
    s.text("U31: push-pull, so CE2 needs no pull-up. R50 10 k (not 100 k): CE2 must stay under 0.2 V on battery", 195, 125, 1.5)
    s.text("against two chips' input leakage; with 3.3 V on U31 still gives at least 2.9 V into it.", 195, 128, 1.5)

    # ---- U32 SRAM rail --------------------------------------------------------------------
    U32 = s.place("megabank:LM66200", "U32", "LM66200", SOT583, 140, 170)
    s.label("+3V3", U32.pin("VIN1")); s.label("BATT+", U32.pin("VIN2"))
    s.glabel("VSRAM", U32.pin("2"), OUT); s.glabel("VSRAM", U32.pin("7"), OUT)
    s.label("GND", U32.pin("~{ON}")); s.nc(U32.pin("ST"))
    s.label("GND", U32.pin("1")); s.label("GND", U32.pin("5"))
    C53 = s.place("Device:C", "C53", "1u", C0603, 180, 185)
    s.glabel("VSRAM", C53.pin("1"), OUT); s.label("GND", C53.pin("2"))
    C54 = s.place("Device:C", "C54", "100n", C0603, 110, 185)
    s.label("BATT+", C54.pin("1")); s.label("GND", C54.pin("2"))
    s.text("U32: not the TPS2115A (55 uA from the cell) and not plain diodes (the rail must sit near 3.3 V while the", 100, 200, 1.5)
    s.text("controller and buffers drive the SRAM). C53 >= 0.1 uF for the LM66200's soft start. ST unused.", 100, 203, 1.5)
    s.text("Check on the prototype: a fresh CR2032 reads up to about 3.3 V open-circuit, close to +3V3; see hardware/README.md.", 100, 206, 1.5)

    BT1 = s.place("Device:Battery_Cell", "BT1", "CR2032", BAT_FP, 60, 170)
    s.label("BATT+", BT1.pin("+")); s.label("GND", BT1.pin("-"))
    F4 = s.place("power:PWR_FLAG", "#FLG15", "PWR_FLAG", "", 40, 160)
    s.label("BATT+", F4.pin("1"))

    # ---- battery monitor ---------------------------------------------------------------
    Q1 = s.place("Transistor_FET:AO3401A", "Q1", "AO3401A", SOT23, 260, 170)
    s.label("BATT+", Q1.pin("S")); s.label("Q1_G", Q1.pin("G")); s.label("BAT_DIV", Q1.pin("D"))
    Q2 = s.place("Transistor_FET:Q_NMOS_GSD", "Q2", "AO3400A", SOT23, 300, 190)
    s.label("Q1_G", Q2.pin("D")); s.glabel("BAT_EN", Q2.pin("G"), IN); s.label("GND", Q2.pin("S"))
    parts = [("R51", "100k", "BAT_DIV", "BAT_ADC"), ("R52", "100k", "BAT_ADC", "GND"),
             ("R53", "1M", "BATT+", "Q1_G"), ("R54", "10k", "BAT_EN", "GND")]
    for k, (ref, val, a, b) in enumerate(parts):
        R = s.place("Device:R", ref, val, R0603, 330 + 15 * k, 160)
        for pin, net in (("1", a), ("2", b)):
            if net in ("BAT_ADC", "BAT_EN"):
                s.glabel(net, R.pin(pin), BI)
            else:
                s.label(net, R.pin(pin))
    C55 = s.place("Device:C", "C55", "100n", C0603, 390, 185)
    s.glabel("BAT_ADC", C55.pin("1"), BI); s.label("GND", C55.pin("2"))
    s.text("Battery monitor: BAT_EN high -> Q2 pulls Q1's gate down -> Q1 connects the cell to R51/R52 (half the cell).", 250, 210, 1.5)
    s.text("Wait 25 ms, average a few ADC readings, BAT_EN low. Off, the cell sees only the MOSFETs' leakage.", 250, 213, 1.5)
    s.text("R54 holds BAT_EN low while the controller is unpowered or booting; R52 holds the ADC pin at 0 V.", 250, 216, 1.5)

    s.write()
    print("wrote power.kicad_sch")


if __name__ == "__main__":
    main()
